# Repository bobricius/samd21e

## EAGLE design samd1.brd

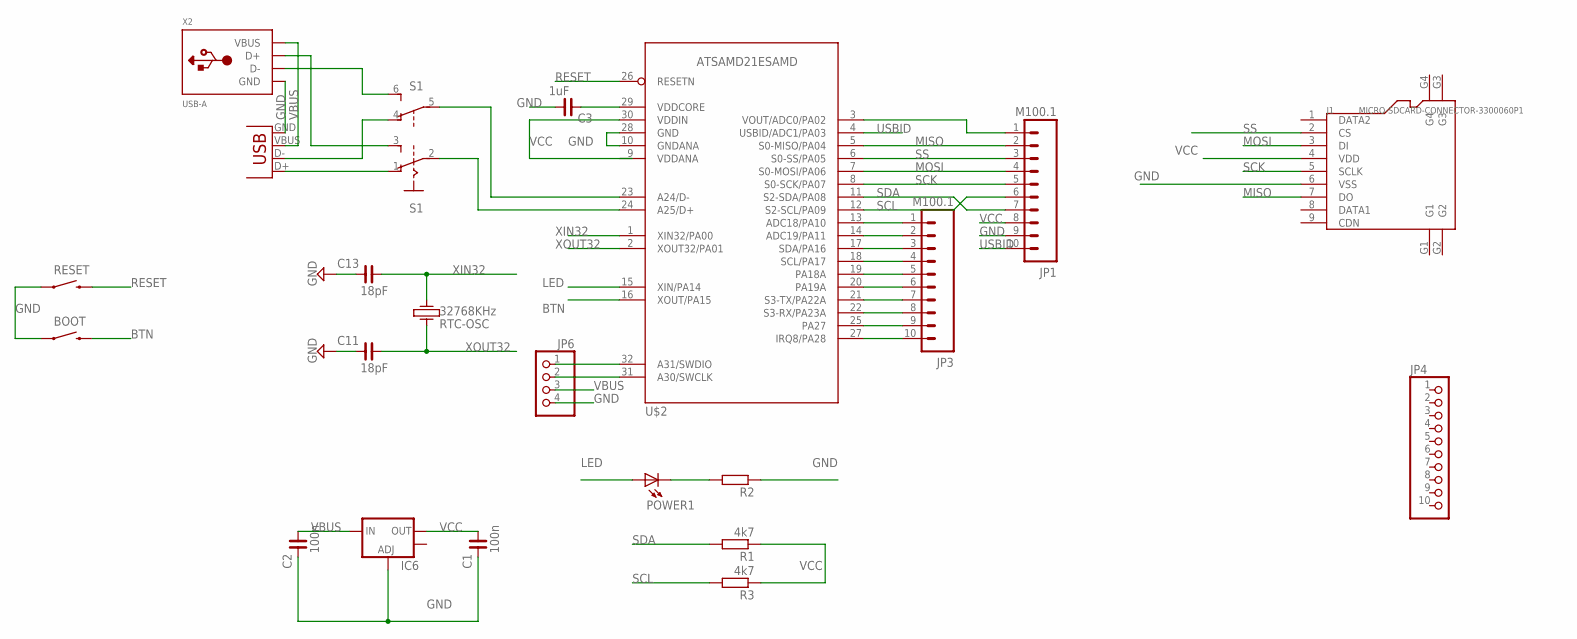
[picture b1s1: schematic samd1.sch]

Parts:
BOOT: SWITCH-MOMENTARY-2-SMD-1101NE; TACTILE-SWITCH-1101NE
C1, C2: 100n; C0603
C3: 1uF; C0603
C11, C13: 18pF; C0603
IC6: V_REG_LM1117SOT223; SOT223
J1: MICRO-SDCARD-CONNECTOR-3300060P1; 9P-SMD-W-RING
JP1, JP3: M100.1; 1X10
JP4: PINHD-1X10; 1X10
JP6: PINHD-1X4/90; 1X04/90
POWER1: Power; LED-0603
R1, R3: 4k7; R0603
R2: R-EU_R0603; R0603
RESET: SWITCH-MOMENTARY-2-SMD-1101NE; TACTILE-SWITCH-1101NE
RTC-OSC: 32768KHz; KX-327LT
S1: A68-A31
U$2: ATSAMD21ESAMD; TQFP32-08
X2: USB-A; MOLEX_480371000
X3: USB_; USB-A-S-SILK-FEMALE

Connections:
BTN: BOOT.P$2 (2), U$2.16 (XOUT/PA15)
GND: BOOT.P$1 (1), C1.2, C2.2, C3.1, C11.2, C13.2, IC6.1 (ADJ), J1.6 (VSS), JP1.9, JP6.4, R2.1, RESET.P$1 (1), U$2.10 (GNDANA), U$2.28 (GND), X2.4 (GND), X3.GND
LED: POWER1.A, U$2.15 (XIN/PA14)
MISO: J1.7 (DO), JP1.2, U$2.5 (S0-MISO/PA04)
MOSI: J1.3 (DI), JP1.4, U$2.7 (S0-MOSI/PA06)
unnamed: JP1.1, U$2.3 (VOUT/ADC0/PA02)
unnamed: S1.2, U$2.24 (A25/D+)
unnamed: C3.2, U$2.29 (VDDCORE)
unnamed: POWER1.C, R2.2
unnamed: JP3.1, U$2.13 (ADC18/PA10)
unnamed: JP3.2, U$2.14 (ADC19/PA11)
unnamed: JP3.3, U$2.17 (SDA/PA16)
unnamed: JP3.4, U$2.18 (SCL/PA17)
unnamed: JP3.5, U$2.19 (PA18A)
unnamed: JP3.6, U$2.20 (PA19A)
unnamed: JP3.7, U$2.21 (S3-TX/PA22A)
unnamed: JP3.8, U$2.22 (S3-RX/PA23A)
unnamed: JP3.9, U$2.25 (PA27)
unnamed: JP3.10, U$2.27 (IRQ8/PA28)
unnamed: S1.5, U$2.23 (A24/D-)
unnamed: S1.6 (S), X2.2 (D-)
unnamed: S1.4 (O), X3.D-
unnamed: S1.3 (S), X2.3 (D+)
unnamed: S1.1 (O), X3.D+
unnamed: JP6.2, U$2.31 (A30/SWCLK)
unnamed: JP6.1, U$2.32 (A31/SWDIO)
RESET: RESET.P$2 (2), U$2.26 (RESETN)
SCK: J1.5 (SCLK), JP1.5, U$2.8 (S0-SCK/PA07)
SCL: JP1.6, R3.2, U$2.12 (S2-SCL/PA09)
SDA: JP1.7, R1.2, U$2.11 (S2-SDA/PA08)
SS: J1.2 (CS), JP1.3, U$2.6 (S0-SS/PA05)
USBID: JP1.10, U$2.4 (USBID/ADC1/PA03)
VBUS: C2.1, IC6.3 (IN), JP6.3, X2.1 (VBUS), X3.VBUS
VCC: C1.1, IC6.2 (OUT), J1.4 (VDD), JP1.8, R1.1, R3.1, U$2.30 (VDDIN)
XIN32: C13.1, RTC-OSC.1, U$2.1 (XIN32/PA00)
XOUT32: C11.1, RTC-OSC.4, U$2.2 (XOUT32/PA01)

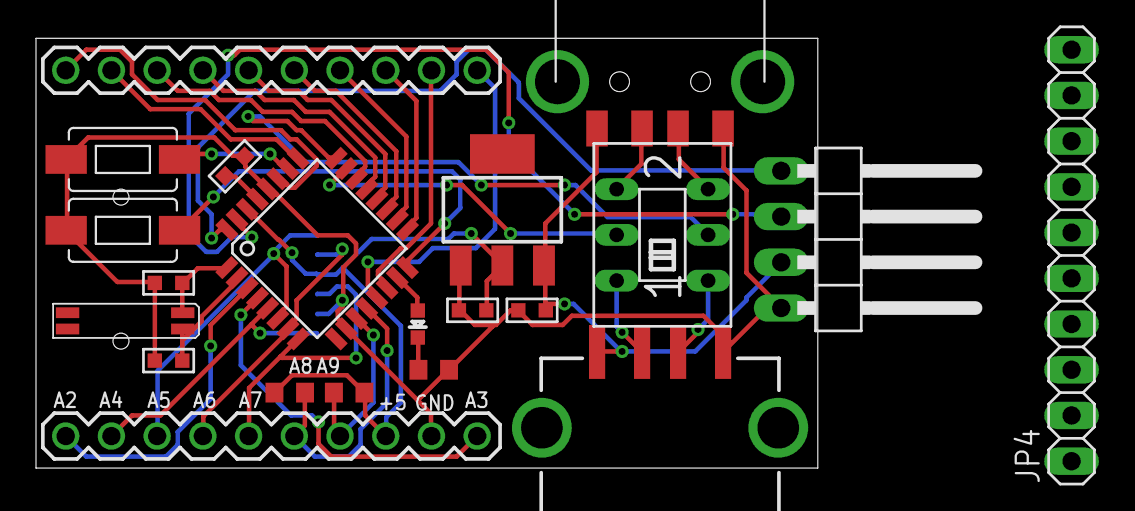
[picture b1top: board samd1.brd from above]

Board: 2 copper layers, 43.4 x 23.9 mm, 22 parts (1 on the bottom side), 36 nets.

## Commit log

2015-03-18 :circus_tent: Added .gitattributes & .gitignore files
2015-03-18 first upload
    alpha version
